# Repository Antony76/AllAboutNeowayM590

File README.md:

# All about Neoway GSM/GPRS modem M590/M590e

This repo started as a "bookmark" to me to bringup this M590 module

 Please start with the Wiki https://github.com/Antony76/AllAboutNeowayM590/wiki

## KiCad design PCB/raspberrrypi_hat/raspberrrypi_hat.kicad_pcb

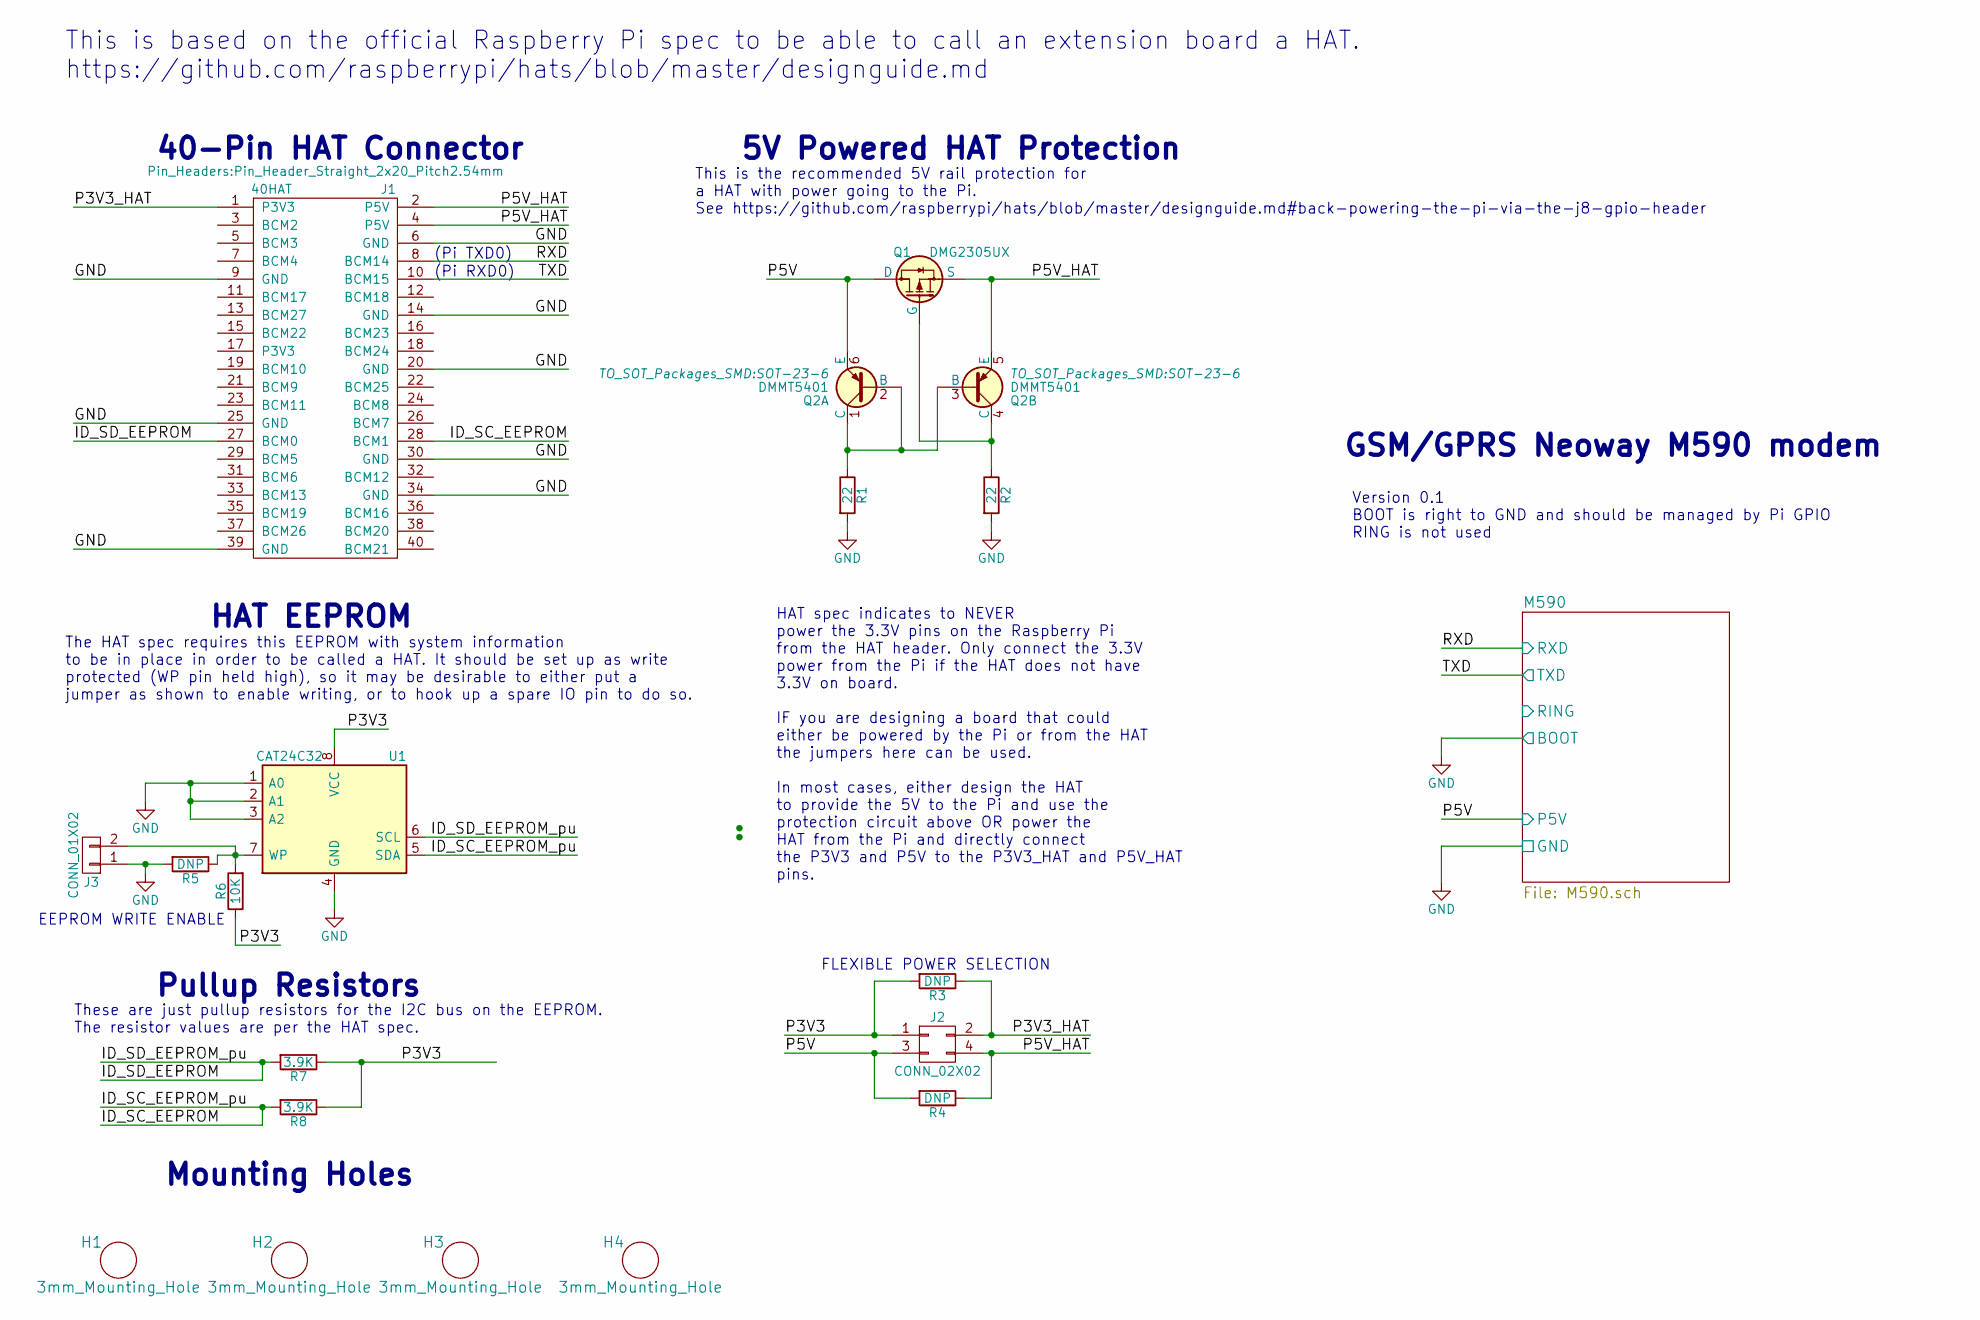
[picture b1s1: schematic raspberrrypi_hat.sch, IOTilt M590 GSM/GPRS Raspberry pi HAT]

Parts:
H1, H2, H3, H4: 3mm_Mounting_Hole; NPTH_3mm_ID
J1: 40HAT; Pin_Header_Straight_2x20_Pitch2.54mm
J2: CONN_02X02; Pin_Header_Straight_2x02_Pitch2.54mm
J3: CONN_01X02; Pin_Header_Straight_1x02_Pitch2.54mm
Q1: DMG2305UX; SOT-23
Q2: DMMT5401; SOT-23-6
R1, R2: 22; R_1206_HandSoldering; MPN RC0402JR-0722RL
R3, R4, R5: DNP; R_1206_HandSoldering; MPN RC0402JR-0722RL
R6: 10K; R_1206_HandSoldering; MPN RC0402JR-0722RL
R7, R8: 3.9K; R_1206_HandSoldering; MPN RC0402JR-0722RL
U1: CAT24C32; SOIC-8_3.9x4.9mm_Pitch1.27mm

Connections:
/ID_SC_EEPROM: J1.28 (BCM1), R8.2, U1.5 (SDA)
/ID_SD_EEPROM: J1.27 (BCM0), R7.2, U1.6 (SCL)
/P3V3: J2.1, R3.2, R6.1, R7.1, R8.1, U1.8 (VCC)
/P3V3_HAT: J1.1 (P3V3), J2.2, R3.1
/P5V: J2.3, Q1.3 (D), Q2.6 (E), R4.2; also elsewhere on the board
/P5V_HAT: J1.2 (P5V), J1.4 (P5V), J2.4, Q1.2 (S), Q2.5 (E), R4.1
/RXD: J1.8 (BCM14); also elsewhere on the board
/TXD: J1.10 (BCM15); also elsewhere on the board
GND: J1.6 (GND), J1.9 (GND), J1.14 (GND), J1.20 (GND), J1.25 (GND), J1.30 (GND), J1.34 (GND), J1.39 (GND), J3.1, R1.2, R2.2, R5.2, U1.1 (A0), U1.2 (A1), U1.3 (A2), U1.4 (GND); also elsewhere on the board
unnamed: J3.2, R5.1, R6.2, U1.7 (WP)
unnamed: Q1.1 (G), Q2.4 (C), R2.1
unnamed: Q2.1 (C), Q2.2 (B), Q2.3 (B), R1.1

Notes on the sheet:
FLEXIBLE POWER SELECTION
5V Powered HAT Protection
This is the recommended 5V rail protection for a HAT with power going to the Pi. See https://github.com/raspberrypi/hats/blob/master/designguide.md#back-powering-the-pi-via-the-j8-gpio-header
EEPROM WRITE ENABLE
Pullup Resistors
HAT EEPROM
Mounting Holes
40-Pin HAT Connector
HAT spec indicates to NEVER power the 3.3V pins on the Raspberry Pi from the HAT header. Only connect the 3.3V power from the Pi if the HAT does not have 3.3V on board. IF you are designing a board that could either be powered by the Pi or from the HAT the jumpers here can be used. In most cases, e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
The HAT spec requires this EEPROM with system information to be in place in order to be called a HAT. It should be set up as write protected (WP pin held high), so it may be desirable to either put a jumper as shown to enable writing, or to hook up a spare IO pin to do so.
These are just pullup resistors for the I2C bus on the EEPROM. The resistor values are per the HAT spec.
This is based on the official Raspberry Pi spec to be able to call an extension board a HAT. https://github.com/raspberrypi/hats/blob/master/designguide.md
(Pi TXD0)
(Pi RXD0)
GSM/GPRS Neoway M590 modem
Version 0.1 BOOT is right to GND and should be managed by Pi GPIO RING is not used

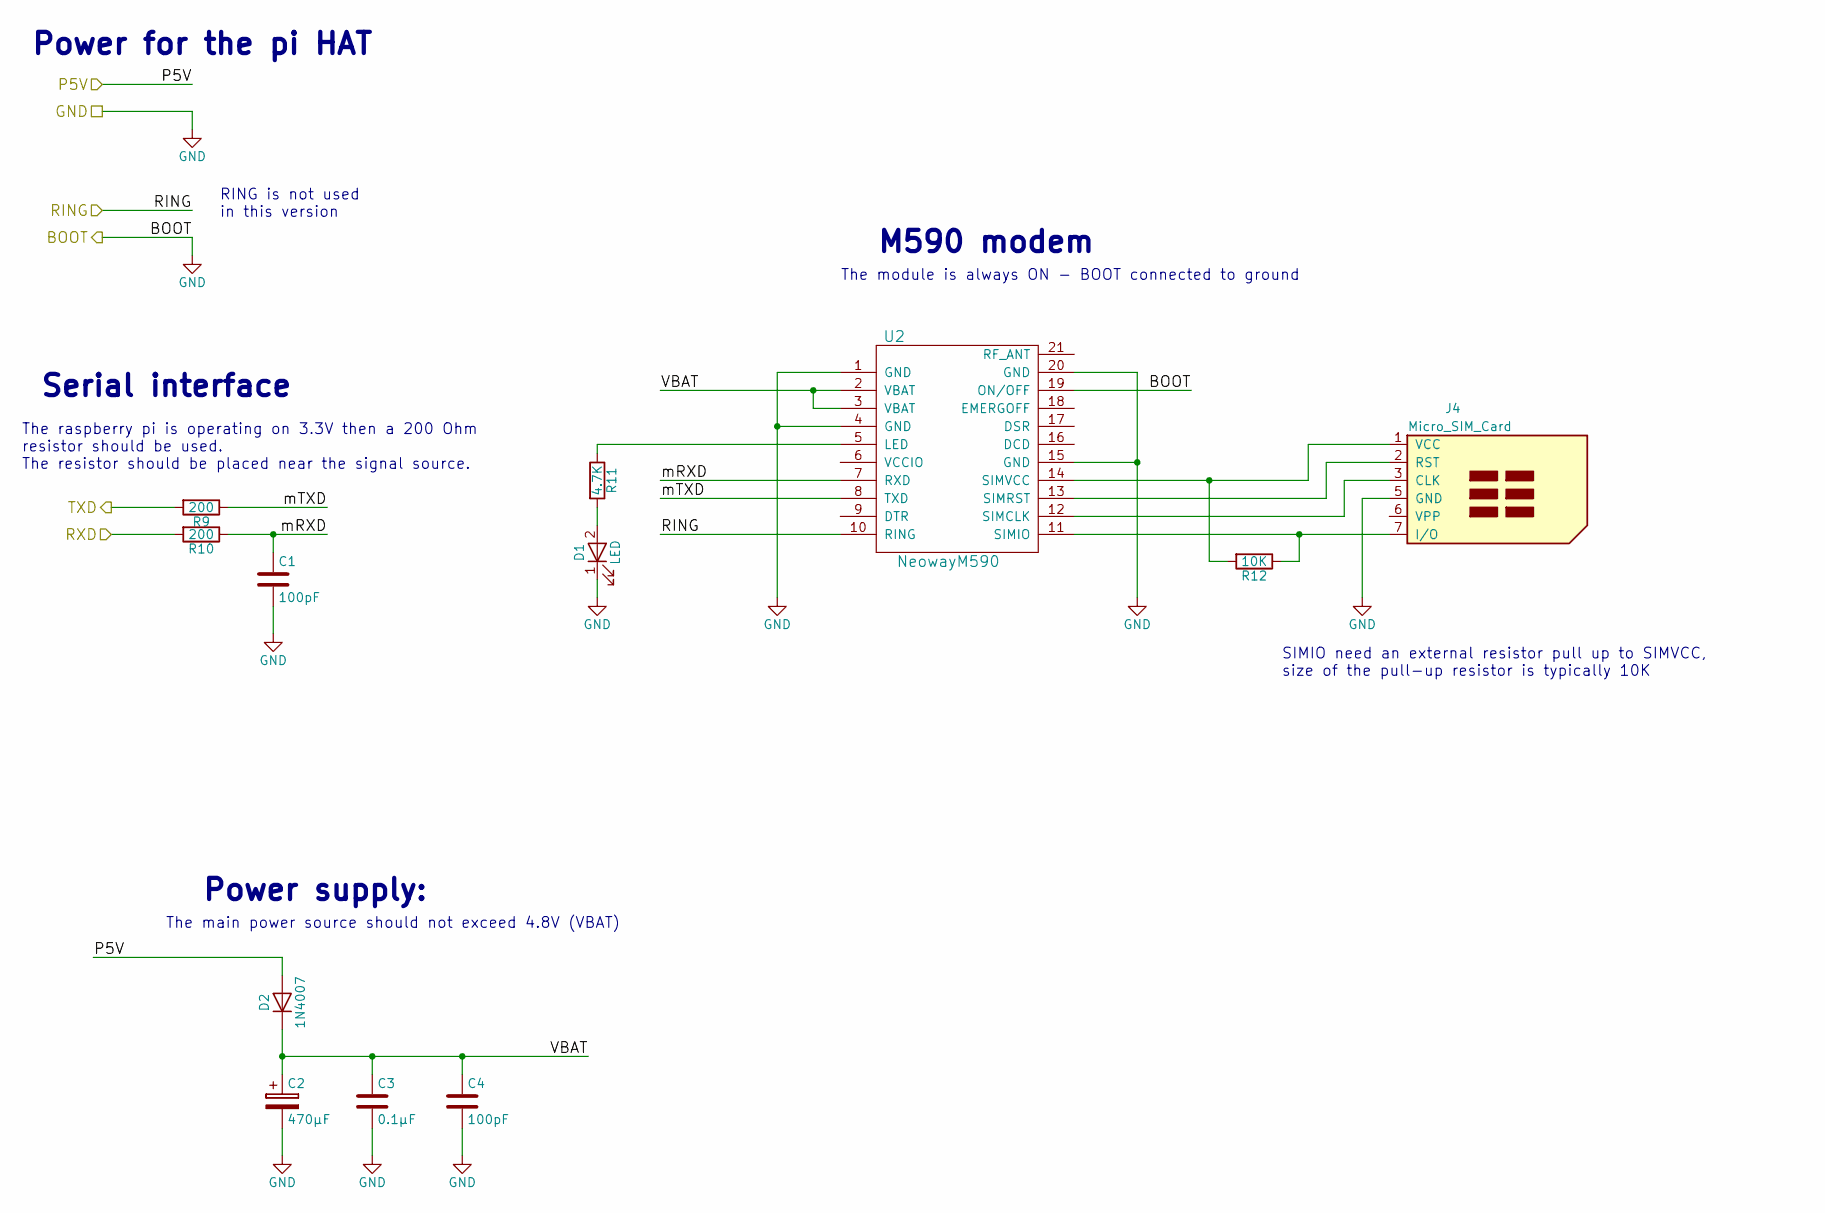
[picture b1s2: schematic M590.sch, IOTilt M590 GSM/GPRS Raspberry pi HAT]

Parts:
C1, C4: 100pF; C_1206_HandSoldering
C2: 470µF; C_1812_HandSoldering
C3: 0.1µF; C_1206_HandSoldering
D1: LED; LED_1206_HandSoldering
D2: 1N4007; D_T-1_P10.16mm_Horizontal
J4: Micro_SIM_Card; MicroSIMSocket
R9, R10: 200; R_1206_HandSoldering
R11: 4.7K; R_1206_HandSoldering
R12: 10K; R_1206_HandSoldering
U2: NeowayM590

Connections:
/M590/VBAT: C2.1, C3.1, C4.1, D2.1 (K), U2.2 (VBAT), U2.3 (VBAT)
/M590/mRXD: C1.1, R10.1, U2.7 (RXD)
/M590/mTXD: R9.1, U2.8 (TXD)
/P5V: D2.2 (A); also elsewhere on the board
/RXD: R10.2; also elsewhere on the board
/TXD: R9.2; also elsewhere on the board
GND: C1.2, C2.2, C3.2, C4.2, D1.1 (K), J4.5 (GND), U2.1 (GND), U2.4 (GND), U2.15 (GND), U2.19 (ON/OFF), U2.20 (GND); also elsewhere on the board
unnamed: D1.2 (A), R11.2
unnamed: J4.1 (VCC), R12.2, U2.14 (SIMVCC)
unnamed: J4.2 (RST), U2.13 (SIMRST)
unnamed: J4.3 (CLK), U2.12 (SIMCLK)
unnamed: J4.7 (I/O), R12.1, U2.11 (SIMIO)
unnamed: R11.1, U2.5 (LED)

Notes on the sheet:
The main power source should not exceed 4.8V (VBAT)
Power supply:
The module is always ON - BOOT connected to ground
M590 modem
The raspberry pi is operating on 3.3V then a 200 Ohm resistor should be used. The resistor should be placed near the signal source.
Serial interface
SIMIO need an external resistor pull up to SIMVCC, size of the pull-up resistor is typically 10K
RING is not used in this version
Power for the pi HAT

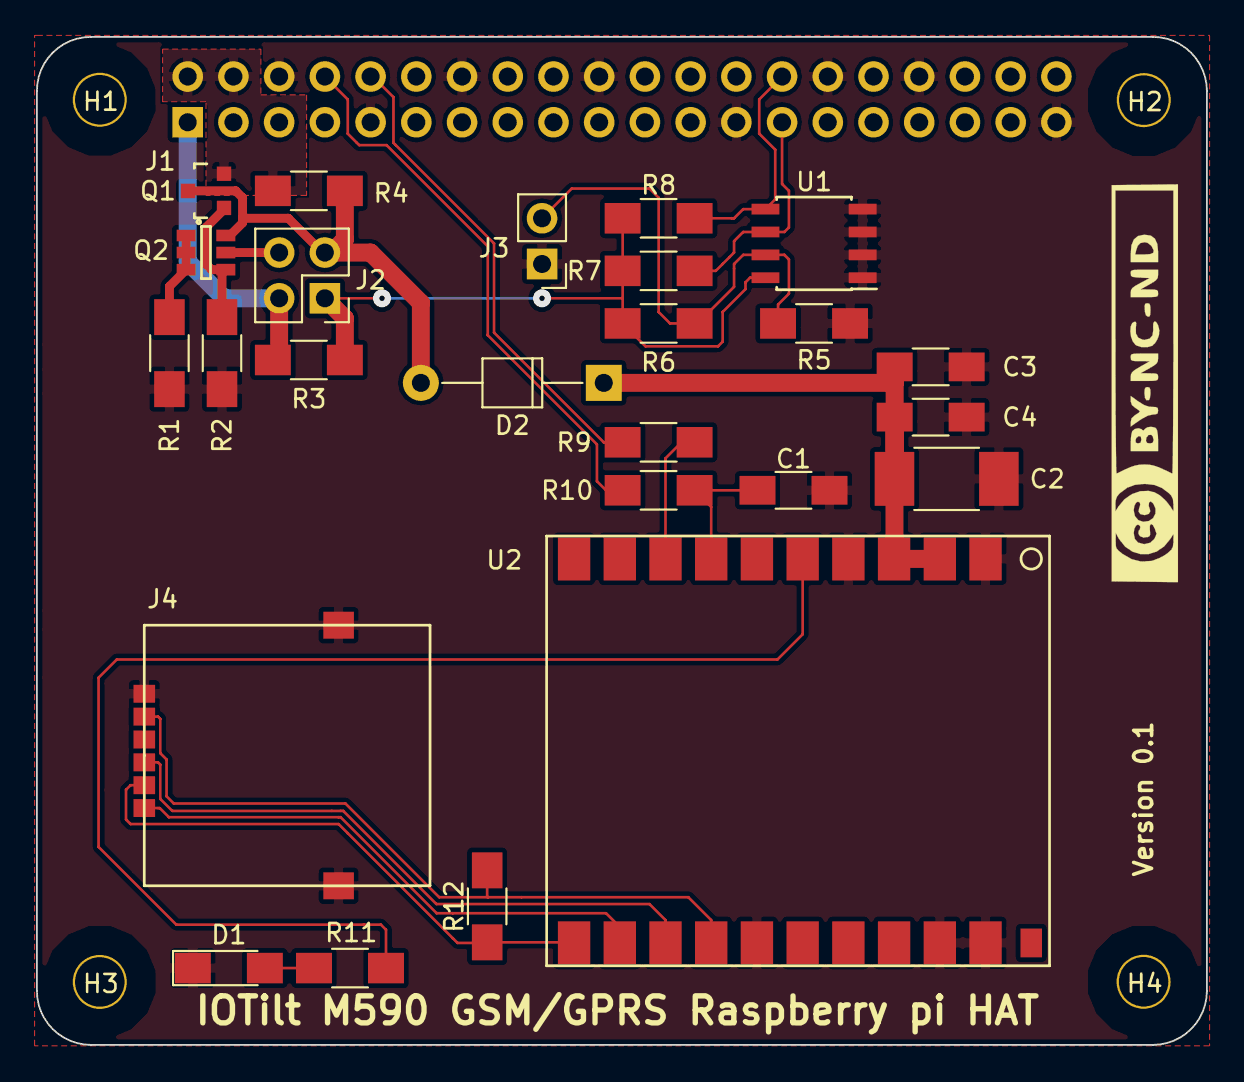
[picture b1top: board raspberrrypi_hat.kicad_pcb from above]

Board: 4 copper layers, 65.0 x 56.0 mm, 30 parts (1 on the bottom side), 21 nets.

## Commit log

2017-06-17 Add 3 usefull documents
2017-06-17 Add PCB copper and top view
2017-06-17 Soldering the DIY kit
2017-06-17 USB to TTL converters
2017-06-21 Raspberry Pi HAT template selected from jonbuford's
2017-06-26 Start to modify Pi_HAT template to add new sheet. Create new M590 component in the library
2017-06-27 Change Pi HAT footprints to SMD 1206_HandSoldering
2017-06-27 Connect hierarchical sheets
2017-06-27 Add .gitignore
2017-06-27 Create NeowayM590 footprint
2017-06-28 Add datasheets of the Pi HAT main components
2017-06-28 Better image to identify the components of the M590 module
2017-06-28 ignore .xcf and .png image formats of this folder
2017-06-28 SCH: M590 and pi wirering
2017-06-29 DS: add Micro SIM socket description to make footprint
2017-06-29 SCH: Change page size to A4, update footer and add comments about parts
2017-07-03 Create Micro-SIM socket footprint
2017-07-03 PCB: Change RPi header + add Micro SIM socket. Starting placement
2017-07-03 Add bck files to .gitignore
2017-07-03 Fix TX/RX serial resistor short-cut by adding mTX/mRX in M590 module sheet
2017-07-04 Add M590 pinout
2017-07-04 PCB: keep on routing
2017-07-05 PCB: routing completed. Reworked alim+eeprom. Add filled zones.
2017-07-05 META: add view of the original routing of alim+eeprom
2017-07-06 PCB: update Micro SIM socket footprint. Move cmp references
2017-07-07 SCH: delete _saved* files
2017-07-09 Creative Commons CC-BY-NC-ND
    This work is licensed under the Creative Commons Attribution-NonCommercial-NoDerivs 3.0 IGO License.
2017-07-09 Mark the project with Creative Commons by-nc-nd license
2017-07-09 PCB: Add small CC-by-nc-nd license logo to PCB front side
2017-07-10 FTP: Fix MicroSimSocket F.Skill + move couple of refs
2017-07-10 PCB: Add description on F.Silks. IOTilt M590 GSM/GPRS Raspberry pi HAT
2017-07-10 SCH: update page title and add CC license on modem sheet
2017-07-10 PCB: Add version 0.1 on F.Silks
2017-07-10 SCH: Fix page title herarchy
2017-07-10 SCH: Fix txt placement about EEPROM WRITE ENABLE
2017-07-16 DOC: Add SIM pinout
2017-07-16 PCB: move components Refs
2017-07-17 Fix .gitignore misplaced
2017-07-17 Change LED footprint to 1206 HandSoldering
2017-07-18 PCB: change via size/diam to 1mm/0.3mm regarding prod requierements
2017-07-28 Fix #3 R11 to D1 connexion issue
2017-07-28 Fix #5 Change R9/R10 to 220R
2017-07-29 Fix #7 Wrong GPIO header footprint
2017-10-18 Add first photo of the PCB raspberry pi HAT rev B+
2017-10-18 Add PCB's photo in the front page
2017-11-17 Fix typo
